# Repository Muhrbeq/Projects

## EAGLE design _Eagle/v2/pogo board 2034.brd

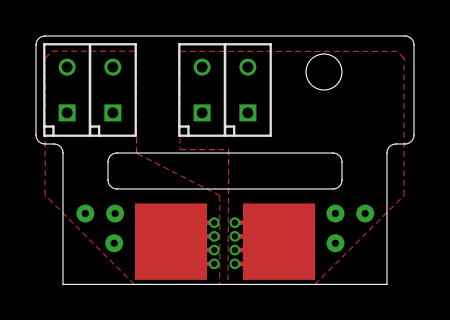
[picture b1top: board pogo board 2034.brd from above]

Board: 2 copper layers, 21.0 x 13.8 mm, 6 parts (0 on the bottom side), 2 nets.

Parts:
U$1, U$2: FLEX_INPUT; FLEX-INPUT
U$3, U$4, U$5, U$6: 821-22-002-10-000101

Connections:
unnamed: U$1.P$1, U$3.1, U$3.2, U$4.1, U$4.2
unnamed: U$2.P$1, U$5.1, U$5.2, U$6.1, U$6.2

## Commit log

2020-09-29 new repo
    moved files to new repo
2020-09-29 Added last of module 2
2020-09-29 Gantt template
2020-10-10 Module 3.1
2020-10-18 Module 4 - done
2020-10-22 Module 5- stage 3
2020-10-22 KRistianstad lab3
2020-10-22 Added json
2020-10-28 Altium Lib
    + Max31855 test code
2020-11-02 PCB components
2020-11-03 Modeul 4
2020-11-04 altium update
2020-11-09 4gll updated
2020-11-11 lib update
2020-11-12 Alitum library and 4gll
2020-11-17 Updated 4GLL + libs
2020-11-18 Update Schematic and Iocfile for 4GLL
2020-11-18 Lab report
2020-11-20 Update altium
2020-11-20 Added footprints
2020-11-20 Almost all pins used
2020-11-24 ouput file added
2020-11-24 Updated 4GLL
2020-11-27 Update c-code
2020-11-30 Moved files
2020-12-01 Added l4g for help
2020-12-01 Summary
2020-12-01 updated with functioning code
2020-12-01 added altium rules
2020-12-01 Started PCB layout
2020-12-04 Altium
2020-12-08 Updated flex symbols
2020-12-08 Added maple
2020-12-08 Maplev2
2020-12-08 Added help files for eurocircuit
2020-12-08 ExegerSolarBoost added
2020-12-15 updated layout
2020-12-17 Small change to Module 6
2020-12-18 Added jst + button
2020-12-18 Lab4 and tenta
2020-12-21 2034
2020-12-21 Lab4Docx
2020-12-21 edit 2034
2021-01-04 Draft1
2021-01-08 c code
2021-01-08 Added zeldaFPC
2021-01-08 Zelda FPC
2021-01-18 Updated altium library and 4gll design
2021-01-19 OPT3001
2021-01-25 Added textparse, CRC, and other basic functionality
2021-01-26 ll v1
2021-01-26 Updated LL
2021-02-02 New PCB & basic code made
2021-02-03 UPdated LLv6
2021-02-04 Update 4GLL layout V2
2021-02-08 Update GPS antenna
2021-02-09 Removed history files, update layout
2021-02-09 2037
2021-02-09 Pcb update minimal
2021-02-16 update before wfh
2021-03-01 Added current consumption for the H2_LL
2021-03-10 Updated altium
2021-03-12 Updated altium design
2021-03-18 Started trace altium
2021-03-18 update school rep
2021-03-19 Traceing altium
2021-03-19 Finish for review
2021-03-29 Updated TMP and Revision control code
2021-03-29 Updated GainDrainINA
2021-04-01 Rewrote TMPcode
    Also wrote code for INA 2 current measeurement test
2021-04-01 Rewrote HDC1080
2021-04-01 ModernLogin
2021-04-07 Nothing major
2021-04-08 Start of navigation
2021-04-09 updated registeruser
2021-04-12 Added new 4gLL code
2021-04-14 Reopen OPT3001 code
2021-04-15 Appdev
2021-04-15 HDC, TMP, OPT, SD, AppDev
2021-04-20 Foldable menu
2021-04-20 4Gll
2021-04-20 New LightController
2021-04-21 Updated LightController
2021-04-22 Changed IVPogos
2021-04-22 Update gerbers and Dxf PogoIV
2021-04-22 Added some functionality to Light
2021-04-23 Updated PCBs
2021-04-23 Added functionality to Lightcalibration
2021-04-26 Added saveLightLevel
2021-04-27 Lightsensor
2021-04-28 Lightsensor complete
2021-04-28 Updated mainwindow
2021-04-29 added functionality
2021-05-06 Headhpone simulator
2021-05-07 LightboxController and HeadphoneSim
2021-05-07 HeadbandSimulator
2021-05-10 Code
2021-05-14 LightSensorCalibration
2021-05-28 Folder change + IVA
2021-05-29 Updated IVA
